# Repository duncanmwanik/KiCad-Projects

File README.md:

# A collection of my some of my PCB projects using KiCAD, with C++ and Flutter software.

# Smart Tap

# Laundry Machine Controller

# Fire Alarm Controller

# Ring Turn Page

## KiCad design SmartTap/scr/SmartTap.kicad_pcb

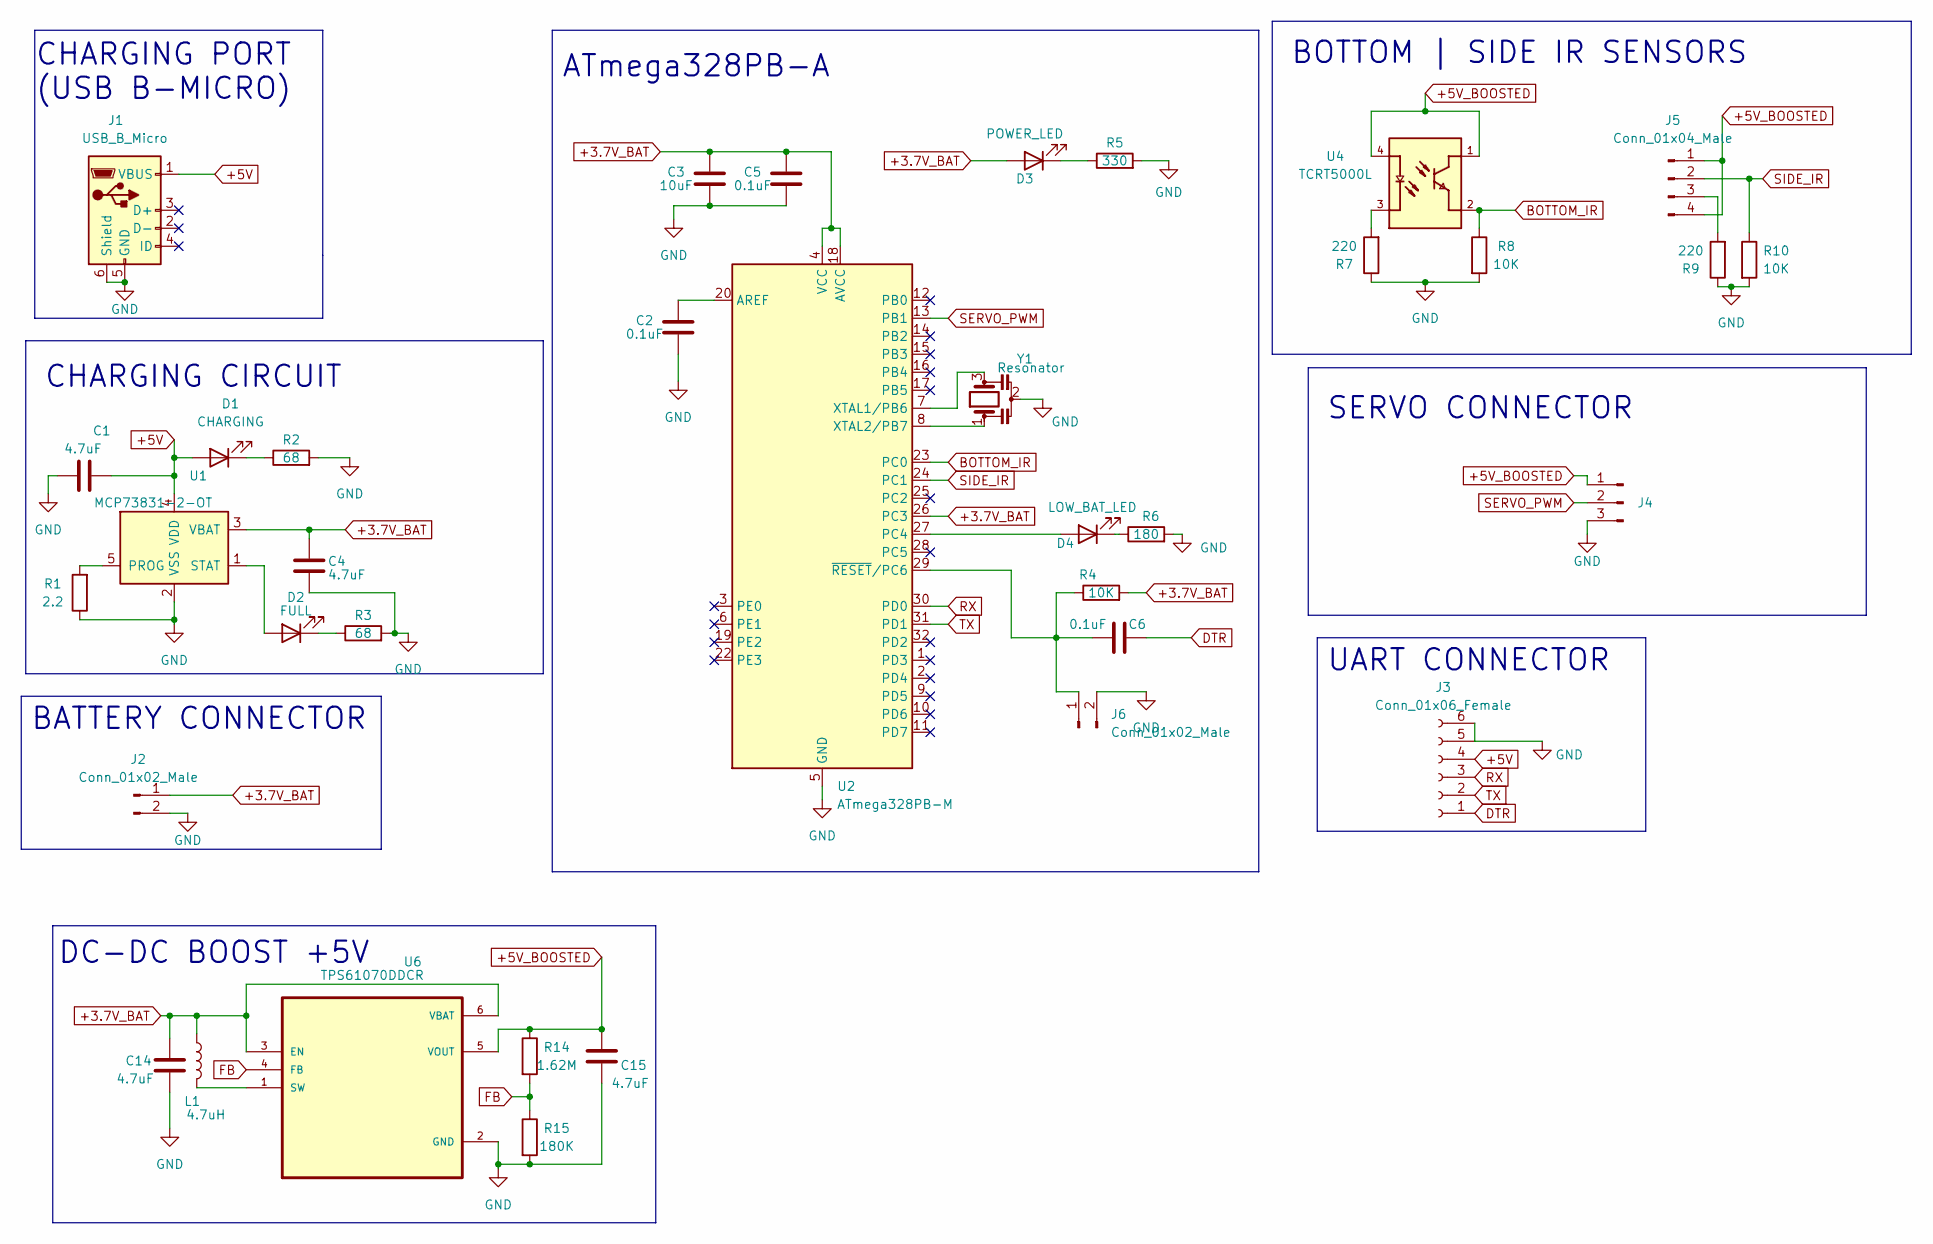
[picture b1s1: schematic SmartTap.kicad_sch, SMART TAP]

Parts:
C1, C4, C14, C15: 4.7uF; C_0402_1005Metric; MPN CL05A475KP5NRNC
C2, C5, C6: 0.1uF; C_0603_1608Metric; MPN CC0603JRNPO9BN200
C3: 10uF; C_0402_1005Metric; MPN CL05A106MQ5NUNC
D1: CHARGING; LED_0603_1608Metric; MPN 19-213/BHC-AP2Q2E/3T
D2: FULL; LED_0603_1608Metric; MPN 19-213/Y2C-CQ2R2L/3T(CY)
D3: POWER_LED; LED_0603_1608Metric; MPN 19-217/R6C-AL1M2VY/3T
D4: LOW_BAT_LED; LED_0603_1608Metric; MPN 19-213SURC/S530-A3/TR8
J1: USB_B_Micro; USB_Micro-B_Molex_47346-0001; MPN 473460001
J2: Conn_01x02_Male; WireConn1x02_P2.54mm
J3: Conn_01x06_Female; PinHeader_1x06_P2.54mm_Vertical; MPN B-2200S06P-A120
J4: Conn_01x03_Male; WireConn1x03_P2.54mm
J5: Conn_01x04_Male; WireConn1x04_P2.54mm
J6: Conn_01x02_Male; PinHeader_1x02_P2.54mm_Vertical
L1: 4.7uH; L_0603_1608Metric; MPN LQM18FN4R7M00D
R1: 2.2; R_0603_1608Metric; MPN 0603WAJ022JT5E
R2, R3: 68; R_0603_1608Metric; MPN 0603WAJ0680T5E
R4, R8, R10: 10K; R_0603_1608Metric; MPN 0603WAJ0103T5E
R5: 330; R_0603_1608Metric; MPN 0603WAJ0331T5E
R6: 180; R_0603_1608Metric; MPN 0603WAJ0181T5E
R7, R9: 220; R_0603_1608Metric; MPN 0603WAJ0221T5E
R14: 1.62M; R_0603_1608Metric; MPN 0603WAF1624T5E
R15: 180K; R_0603_1608Metric; MPN 0603WAF1803T5E
U1: MCP73831-2-OT; SOT-23-5; MPN MCP73831T-2ATI/OT
U2: ATmega328PB-M; QFN-32-1EP_5x5mm_P0.5mm_EP3.1x3.1mm; MPN ATMEGA328PB-MU
U4: TCRT5000L; XDCR_TCRT5000L
U6: TPS61070DDCR; SOT-23-6; MPN TPS61070DDCR
Y1: Resonator; OSC_CSTCE16M0V53-R0; MPN S2216000091080

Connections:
+3.7V_BAT: C3.2, C4.1, C5.2, C14.1, D3.2 (A), J2.1, L1.1, R4.2, U1.3 (VBAT), U2.4 (VCC), U2.18 (AVCC), U2.26 (PC3), U6.3 (EN), U6.6 (VBAT)
+5V: C1.2, D1.2 (A), J1.1 (VBUS), J3.4, U1.4 (VDD)
+5V_BOOSTED: C15.1, J4.1, J5.1, J5.4, R14.1, U4.1, U4.4, U6.5 (VOUT)
BOTTOM_IR: R8.1, U2.23 (PC0), U4.2
DTR: C6.2, J3.1
FB: R14.2, R15.1, U6.4 (FB)
GND: C1.1, C2.1, C3.1, C4.2, C5.1, C14.2, C15.2, J1.5 (GND), J1.6 (Shield), J2.2, J3.5, J3.6, J4.3, J6.2, R1.1, R2.2, R3.2, R5.2, R6.2, R7.1, R8.2, R9.1, R10.2, R15.2, U1.2 (VSS), U2.5 (GND), U2.21 (GND), U2.33 (GND), U6.2 (GND), Y1.2
unnamed: C2.2, U2.20 (AREF)
unnamed: C6.1, J6.1, R4.1, U2.29 (~RESET/PC6)
unnamed: D2.1 (K), R3.1
unnamed: D2.2 (A), U1.1 (STAT)
unnamed: D3.1 (K), R5.1
unnamed: D4.1 (K), R6.1
unnamed: D4.2 (A), U2.27 (PC4)
unnamed: J5.3, R9.2
unnamed: L1.2, U6.1 (SW)
unnamed: R1.2, U1.5 (PROG)
unnamed: D1.1 (K), R2.1
unnamed: R7.2, U4.3
unnamed: U2.7 (XTAL1/PB6), Y1.3
unnamed: U2.8 (XTAL2/PB7), Y1.1
RX: J3.3, U2.30 (PD0)
SERVO_PWM: J4.2, U2.13 (PB1)
SIDE_IR: J5.2, R10.1, U2.24 (PC1)
TX: J3.2, U2.31 (PD1)

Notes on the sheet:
SERVO CONNECTOR
CHARGING PORT (USB B-MICRO)
BOTTOM | SIDE IR SENSORS
DC-DC BOOST +5V
CHARGING CIRCUIT
BATTERY CONNECTOR
ATmega328PB-A
UART CONNECTOR

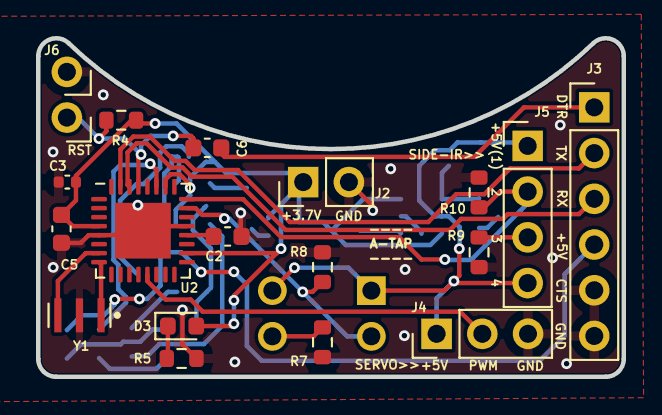
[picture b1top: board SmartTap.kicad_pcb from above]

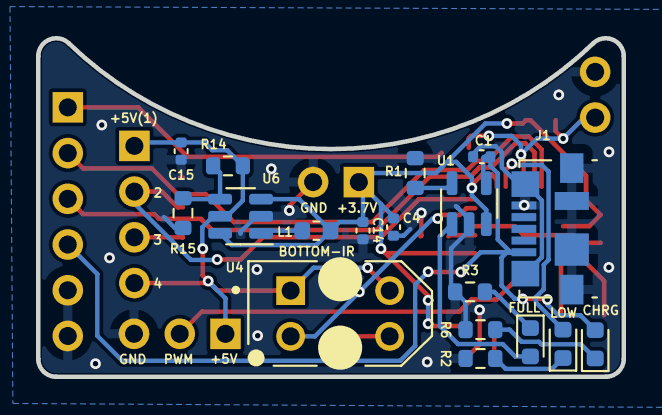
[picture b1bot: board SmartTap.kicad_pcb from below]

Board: 2 copper layers, 32.5 x 18.8 mm, 36 parts (18 on the bottom side), 25 nets.

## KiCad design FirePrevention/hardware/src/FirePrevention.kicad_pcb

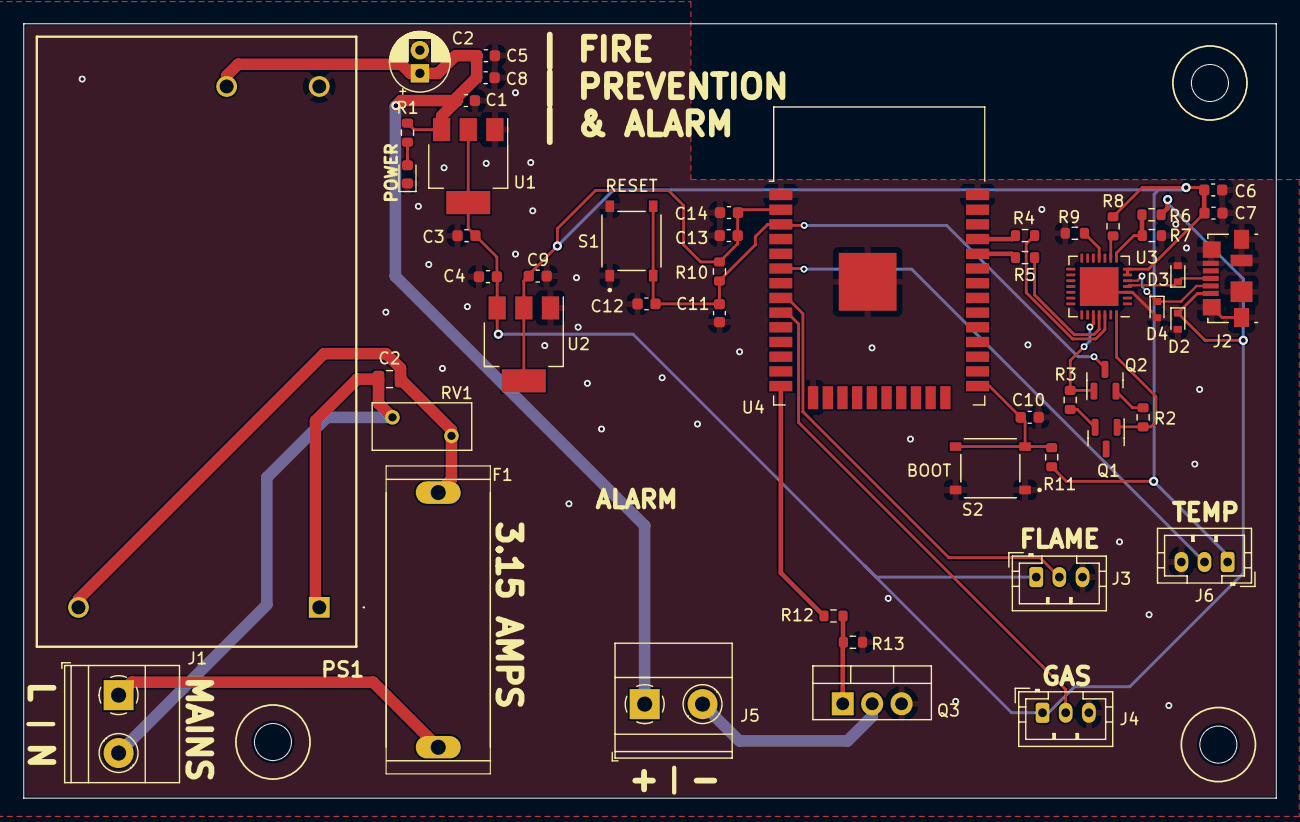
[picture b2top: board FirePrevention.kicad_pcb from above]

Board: 2 copper layers, 108.2 x 66.9 mm, 50 parts (0 on the bottom side), 29 nets.

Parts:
C1, C3, C5: 10uF/10V/10%; C_0603_1608Metric
C2: 22uF/50V/20%; CP_Radial_D5.0mm_P2.00mm
C2#2: 100nF; C_0805_2012Metric
C4, C8, C9, C14: 22uF/10V/10%; C_0603_1608Metric
C6: 4.7uF/50v; C_0603_1608Metric
C7, C10, C12: 0.1uF/50v; C_0603_1608Metric
C11: 0.1uF; C_0603_1608Metric
C13: 100nF/10V/10%; C_0603_1608Metric
D1: 12V; LED_0603_1608Metric
D2, D3, D4: D_TVS_Filled; D_SOD-523
F1: MC000827
J1: MAINS; TerminalBlock_Phoenix_MKDS-1,5-2_1x02_P5.00mm_Horizontal
J2: USB_B_Micro; USB_Micro-B_Molex_47346-0001
J3: FLAME_SENSOR_KYO26; JST_PH_B3B-PH-K_1x03_P2.00mm_Vertical
J4: GAS_SENSOR_MQ2; JST_PH_B3B-PH-K_1x03_P2.00mm_Vertical
J5: ALARM_SIREN_12V; TerminalBlock_Phoenix_MKDS-1,5-2_1x02_P5.00mm_Horizontal
J6: TEMPERATURE_SENSOR_DHT22; JST_PH_B3B-PH-K_1x03_P2.00mm_Vertical
PS1: RAC20E-12SK_277; RAC20E12SK277
Q1, Q2: SS8050; SOT-23
Q3: IRLZ44N; TO-220-3_Vertical
R1: 2k; R_0603_1608Metric
R2, R3, R10, R11: 10k; R_0603_1608Metric
R4, R5: 0R; R_0603_1608Metric
R6: 22.1K; R_0603_1608Metric
R7: 47.5K; R_0603_1608Metric
R8: 2K; R_0603_1608Metric
R9: 10K; R_0603_1608Metric
R12: 220/10V/5%; R_0603_1608Metric
R13: 47K/10V/5%; R_0603_1608Metric
RV1: Varistor; Fuse_BelFuse_0ZRE0005FF_L8.3mm_W3.8mm
S1, S2: TS-1187A-B-A-B; SW_TS-1187A-B-A-B
U1: AMS1117-5.0; SOT-223-3_TabPin2
U2: AMS1117-3.3; SOT-223-3_TabPin2
U3: CP2102N-Axx-xQFN28; QFN-28-1EP_5x5mm_P0.5mm_EP3.35x3.35mm
U4: ESP32-S; ESP32-WROOM-32

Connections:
+3V3: C6.2, C7.2, C9.1, C13.1, C14.1, J6.1, R8.2, R10.1, R11.1, U2.2 (VO), U3.6 (VDD), U3.7 (VREGIN), U4.2 (VDD)
+5V: C3.1, C4.1, D2.1 (A1), J2.1 (VBUS), J3.1, J4.1, R6.1, U1.2 (VO), U2.3 (VI)
+12V: C1.1, C2.1, C5.1, C8.1, J5.1, PS1.3 (_+VOUT), R1.1, U1.3 (VI)
/ALARM: R12.1, U4.14 (IO12)
/DTR: Q1.1 (E), R2.1, U3.28 (~DTR)
/EN: C11.1, C12.2, Q2.3 (C), R10.2, S1.C, S1.D, U4.3 (EN)
/FLAME: J3.2, U4.8 (IO32)
/GAS: J4.2, U4.9 (IO33)
/IO0: C10.2, R11.2, S2.C, S2.D, U4.25 (IO0)
/RTS: Q2.1 (E), R3.1, U3.24 (~RTS)
/RXD: R5.2, U3.25 (RXD)
/RXD0: R5.1, U4.34 (RXD0/IO3)
/TEMP: J6.2, U4.6 (IO34)
/TXD: R4.2, U3.26 (TXD)
/TXD0: R4.1, U4.35 (TXD0/IO1)
/USB_DN: D4.1 (A1), J2.2 (D-), U3.5 (D-)
/USB_DP: D3.1 (A1), J2.3 (D+), U3.4 (D+)
GND: C1.2, C2.2, C3.2, C4.2, C5.2, C6.1, C7.1, C8.2, C9.2, C10.1, C11.2, C12.1, C13.2, C14.2, D1.1 (K), D2.2 (A2), D3.2 (A2), D4.2 (A2), J2.5 (GND), J2.6 (Shield), J3.3, J4.3, J6.3, PS1.4 (-VOUT), Q3.3 (S), R7.1, R9.2, R13.1, S1.A, S1.B, S2.A, S2.B, U1.1 (GND), U2.1 (GND), U3.3 (GND), U3.29 (GND), U4.1 (GND), U4.15 (GND), U4.38 (GND), U4.39 (GND)
unnamed: D1.2 (A), R1.2
unnamed: F1.P$2, PS1.2 (VAC_IN_(L)), RV1.1
unnamed: F1.P$1, J1.1
unnamed: J1.2, PS1.1 (VAC_IN_(N)), RV1.2
unnamed: J5.2, Q3.2 (D)
unnamed: Q1.2 (B), R3.2
unnamed: Q2.2 (B), R2.2
unnamed: Q3.1 (G), R12.2, R13.2
unnamed: R6.2, R7.2, U3.8 (VBUS)
unnamed: R8.1, U3.9 (~RST)
unnamed: R9.1, U3.11 (~SUSPEND)

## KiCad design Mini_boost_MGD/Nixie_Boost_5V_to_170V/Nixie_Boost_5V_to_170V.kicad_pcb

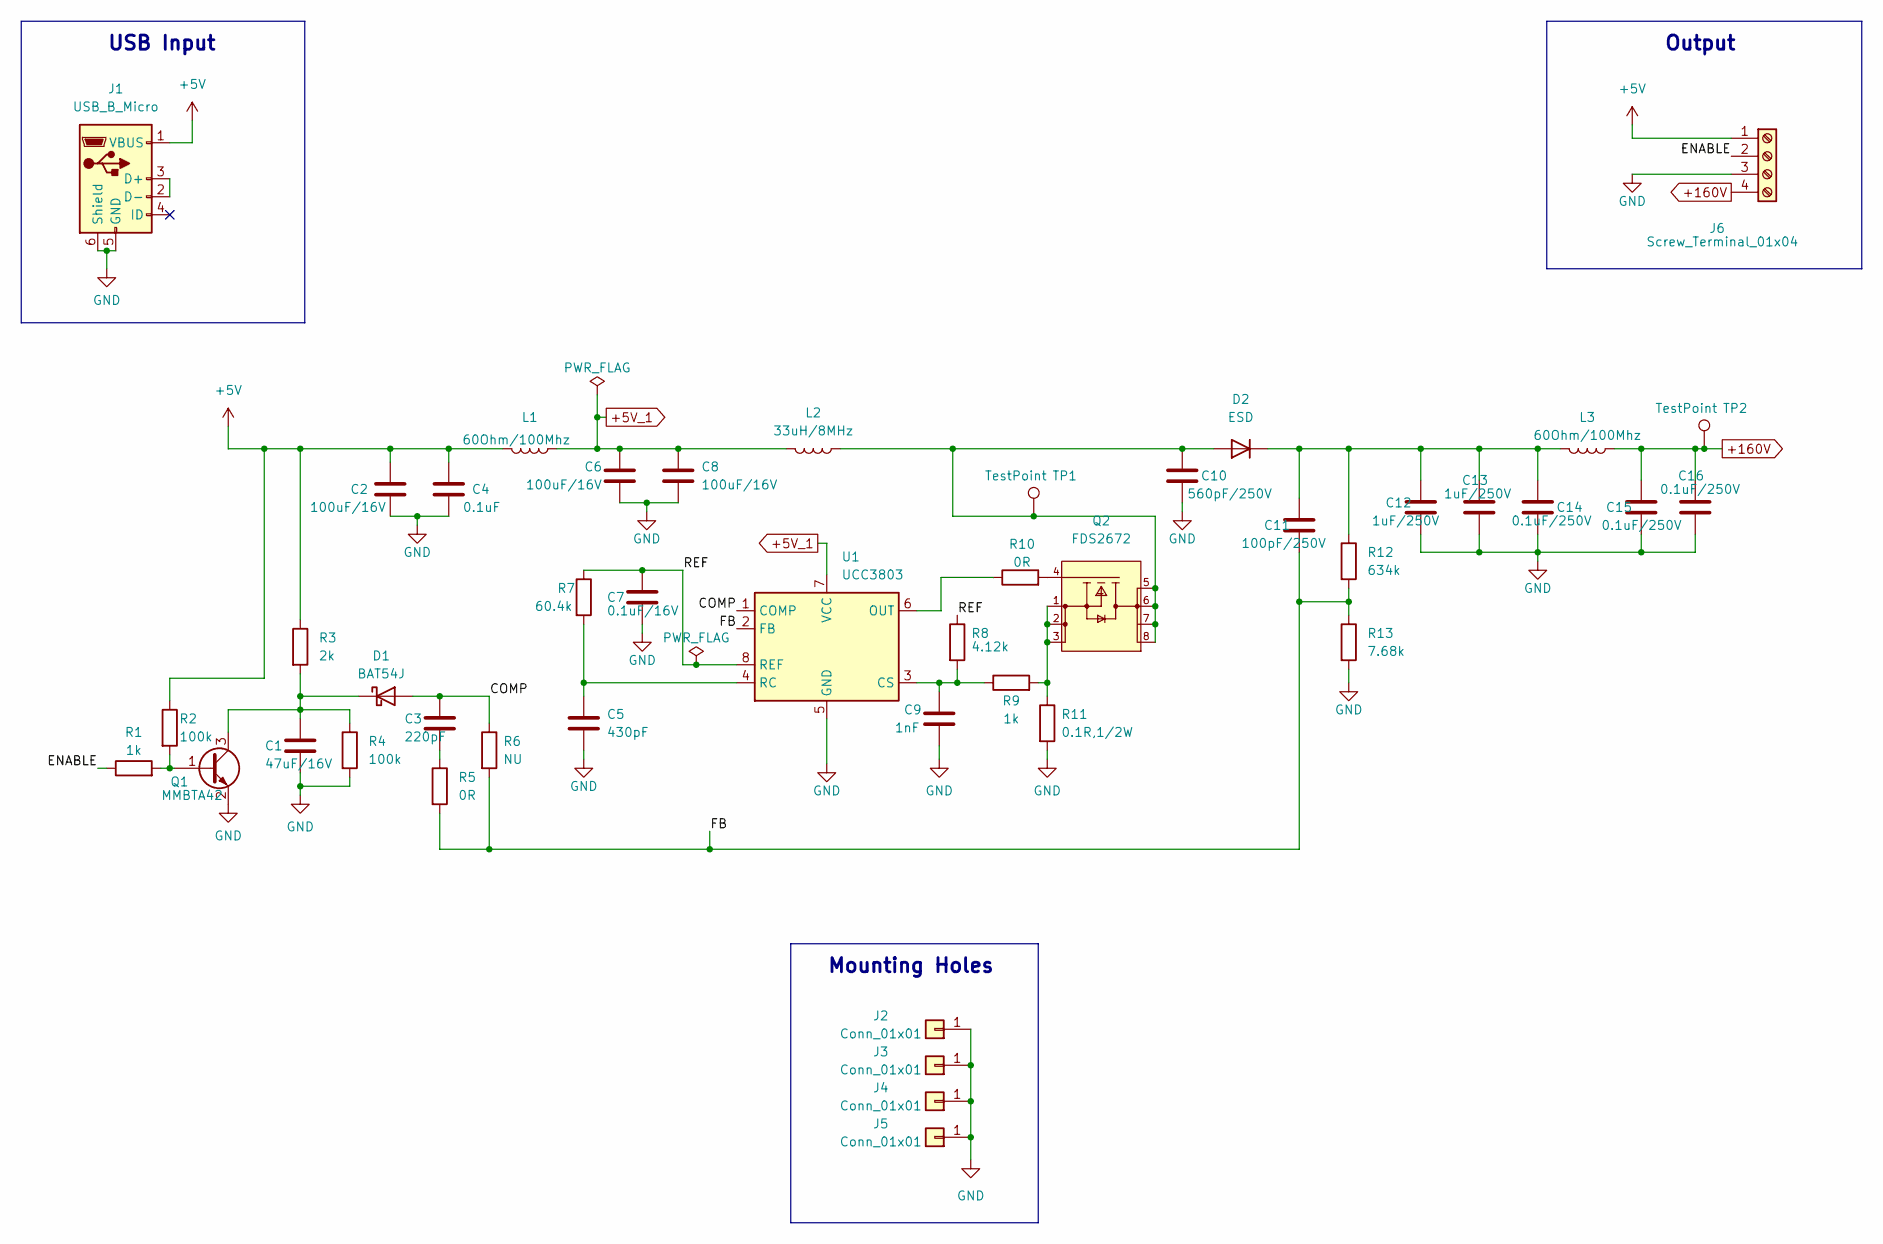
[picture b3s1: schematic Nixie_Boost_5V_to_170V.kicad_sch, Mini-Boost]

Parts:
C1: 47uF/16V; C_1206_3216Metric
C2, C6, C8: 100uF/16V; C_1210_3225Metric
C3: 220pF; C_0805_2012Metric
C4: 0.1uF; C_0805_2012Metric
C5: 430pF; C_0805_2012Metric
C7: 0.1uF/16V; C_0805_2012Metric
C9: 1nF; C_0805_2012Metric
C10: 560pF/250V; C_0603_1608Metric
C11: 100pF/250V; C_0805_2012Metric
C12, C13: 1uF/250V; C_0805_2012Metric
C14, C15, C16: 0.1uF/250V; C_0805_2012Metric
D1: BAT54J; D_SOD-323F
D2: ESD; D_SMA
J1: USB_B_Micro; USB_Micro-B_Molex_47346-0001
J2, J3, J4, J5: Conn_01x01; MountingHole_2.2mm_M2_Pad_Via
J6: Screw_Terminal_01x04; TerminalBlock_Phoenix_PT-1,5-4-3.5-H_1x04_P3.50mm_Horizontal
L1, L3: 60Ohm/100Mhz; L_0805_2012Metric; MPN BKP2125HS600-T
L2: 33uH/8MHz; L_12x12mm_H6mm; MPN 7447709330
Q1: MMBTA42; SOT-23
Q2: FDS2672; SOIC-8-1EP_3.9x4.9mm_P1.27mm_EP2.29x3mm
R1, R9: 1k; R_0805_2012Metric
R2, R4: 100k; R_0805_2012Metric
R3: 2k; R_0805_2012Metric
R5, R10: 0R; R_0805_2012Metric
R6: NU; R_0805_2012Metric
R7: 60.4k; R_0805_2012Metric
R8: 4.12k; R_0805_2012Metric
R11: 0.1R,1/2W; R_0805_2012Metric
R12: 634k; R_0805_2012Metric
R13: 7.68k; R_0805_2012Metric
TP1, TP2: TestPoint; TestPoint_Pad_D1.0mm
U1: UCC3803; SOIC-8-1EP_3.9x4.9mm_P1.27mm_EP2.29x3mm

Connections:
+5V: C2.1, C4.1, J1.1 (VBUS), J6.1, L1.2, R2.1, R3.1
+5V_1: C6.1, C8.1, L1.1, L2.2, U1.7 (VCC)
+160V: C15.1, C16.1, J6.4, L3.1, TP2.1
/COMP: C3.1, D1.2 (A), R6.1, U1.1 (COMP)
/ENABLE: J6.2, R1.1
/FB: C11.2, R5.2, R6.2, R12.2, R13.1, U1.2 (FB)
/REF: C7.1, R7.1, R8.1, U1.8 (REF)
GND: C1.2, C2.2, C4.2, C5.2, C6.2, C7.2, C8.2, C9.2, C10.2, C12.2, C13.2, C14.2, C15.2, C16.2, J1.5 (GND), J1.6 (Shield), J2.1, J3.1, J4.1, J5.1, J6.3, Q1.2 (E), R4.2, R11.2, R13.2, U1.5 (GND)
unnamed: C1.1, D1.1 (K), Q1.3 (C), R3.2, R4.1
unnamed: C3.2, R5.1
unnamed: C5.1, R7.2, U1.4 (RC)
unnamed: C9.1, R8.2, R9.1, U1.3 (CS)
unnamed: C10.1, D2.2 (A), L2.1, Q2.5 (D), Q2.6 (D), Q2.7 (D), Q2.8 (D), TP1.1
unnamed: C11.1, C12.1, C13.1, C14.1, D2.1 (K), L3.2, R12.1
unnamed: J1.2 (D-), J1.3 (D+)
unnamed: Q1.1 (B), R1.2, R2.2
unnamed: Q2.1 (S), Q2.2 (S), Q2.3 (S), R9.2, R11.1
unnamed: Q2.4 (S), R10.2
unnamed: R10.1, U1.6 (OUT)

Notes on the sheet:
USB Input
Mounting Holes
Output

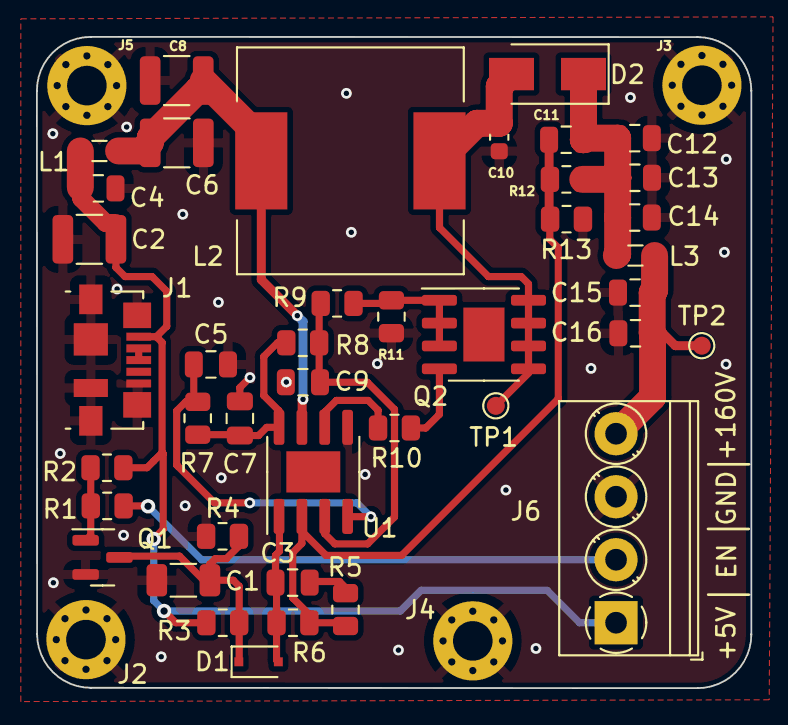
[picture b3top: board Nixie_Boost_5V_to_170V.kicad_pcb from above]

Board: 2 copper layers, 39.7 x 36.2 mm, 45 parts (0 on the bottom side), 19 nets.

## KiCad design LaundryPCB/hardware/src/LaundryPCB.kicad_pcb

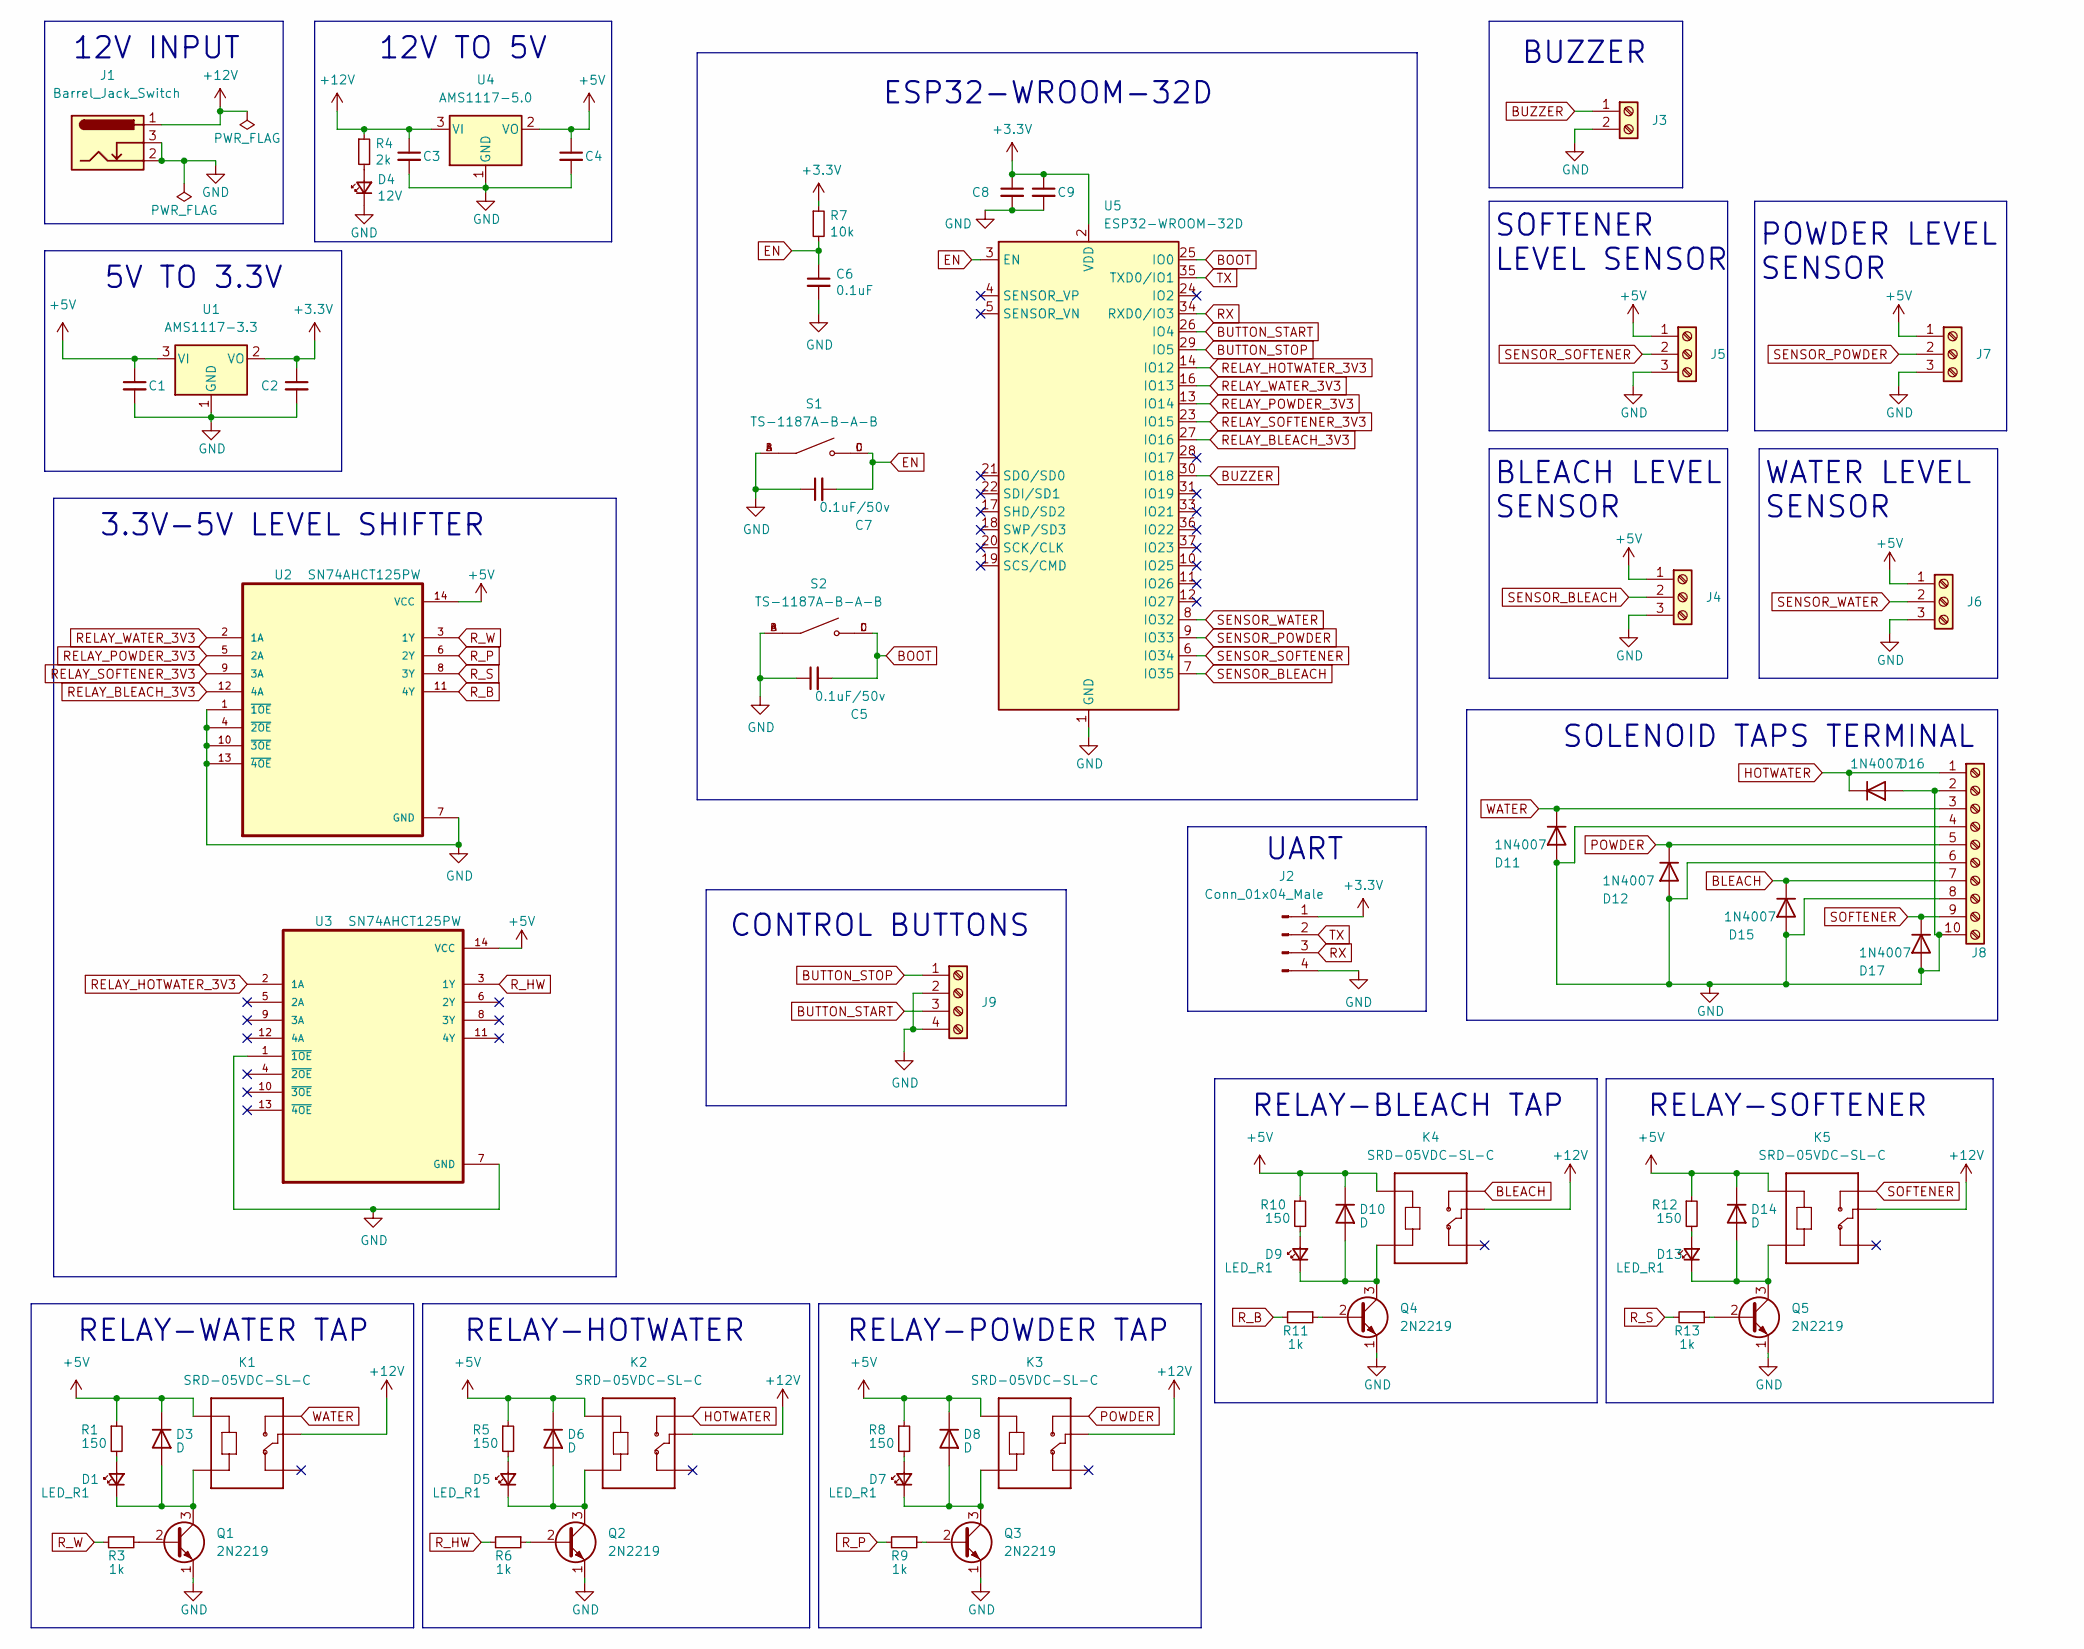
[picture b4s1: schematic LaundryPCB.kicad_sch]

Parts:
C1, C2, C9: 22uF/10V/10%; C_0603_1608Metric
C3, C4: 10uF/10V/10%; C_0603_1608Metric
C5, C7: 0.1uF/50v; C_0603_1608Metric
C6: 0.1uF; C_0603_1608Metric
C8: 100nF/10V/10%; C_0603_1608Metric
D1, D5, D7, D9, D13: LED_R1; LED_0603_1608Metric
D3, D6, D8, D10, D14: D; D_0603_1608Metric
D4: 12V; LED_0603_1608Metric
D11, D12, D15, D16, D17: 1N4007; D_DO-41_SOD81_P10.16mm_Horizontal
J1: Barrel_Jack_Switch; BarrelJack_Horizontal
J2: Conn_01x04_Male; PinHeader_1x04_P2.54mm_Vertical
J3: Screw_Terminal_01x02; TerminalBlock_Phoenix_MKDS-3-2-5.08_1x02_P5.08mm_Horizontal
J4, J5, J6, J7: Screw_Terminal_01x03; TerminalBlock_Phoenix_MKDS-3-3-5.08_1x03_P5.08mm_Horizontal
J8: Screw_Terminal_01x10; TerminalBlock_Phoenix_MKDS-1,5-10-5.08_1x10_P5.08mm_Horizon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
J9: Screw_Terminal_01x04; TerminalBlock_Phoenix_MKDS-1,5-4-5.08_1x04_P5.08mm_Horizont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
K1, K2, K3, K4, K5: SRD-05VDC-SL-C; RELAY_SRD-05VDC-SL-C
Q1, Q2, Q3, Q4, Q5: 2N2219; SOT-23
R1, R5, R8, R10, R12: 150; R_0603_1608Metric
R3, R6, R9, R11, R13: 1k; R_0603_1608Metric
R4: 2k; R_0603_1608Metric
R7: 10k; R_0603_1608Metric
S1, S2: TS-1187A-B-A-B; SW_TS-1187A-B-A-B; PARTREV A0
U1: AMS1117-3.3; SOT-223-3_TabPin2
U2, U3: SN74AHCT125PW; SOP65P640X120-14N
U4: AMS1117-5.0; SOT-223-3_TabPin2
U5: ESP32-WROOM-32D; ESP32-WROOM-32

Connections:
+3V3: C2.1, C8.1, C9.1, J2.1, R7.1, U1.2 (VO), U5.2 (VDD)
+5V: C1.1, C4.1, D3.1 (K), D6.1 (K), D8.1 (K), D10.1 (K), D14.1 (K), J4.1, J5.1, J6.1, J7.1, K1.A1, K2.A1, K3.A1, K4.A1, K5.A1, R1.1, R5.1, R8.1, R10.1, R12.1, U1.3 (VI), U2.14 (VCC), U3.14 (VCC), U4.2 (VO)
+12V: C3.1, J1.1, K1.COM, K2.COM, K3.COM, K4.COM, K5.COM, R4.1, U4.3 (VI)
BLEACH: D15.1 (K), J8.7, K4.NO
BOOT: C5.2, S2.C, S2.D, U5.25 (IO0)
BUTTON_START: J9.3, U5.26 (IO4)
BUTTON_STOP: J9.1, U5.29 (IO5)
BUZZER: J3.1, U5.30 (IO18)
EN: C6.1, C7.2, R7.2, S1.C, S1.D, U5.3 (EN)
GND: C1.2, C2.2, C3.2, C4.2, C5.1, C6.2, C7.1, C8.2, C9.2, D4.1 (K), D11.2 (A), D12.2 (A), D15.2 (A), D16.2 (A), D17.2 (A), J1.2, J1.3, J2.4, J3.2, J4.3, J5.3, J6.3, J7.3, J8.2, J8.4, J8.6, J8.8, J8.10, J9.2, J9.4, Q1.1 (E), Q2.1 (E), Q3.1 (E), Q4.1 (E), Q5.1 (E), S1.A, S1.B, S2.A, S2.B, U1.1 (GND), U2.1 (~1OE), U2.4 (~2OE), U2.7 (GND), U2.10 (~3OE), U2.13 (~4OE), U3.1 (~1OE), U3.7 (GND), U4.1 (GND), U5.1 (GND), U5.15 (GND), U5.38 (GND), U5.39 (GND)
HOTWATER: D16.1 (K), J8.1, K2.NO
unnamed: D1.1 (K), D3.2 (A), K1.A2, Q1.3 (C)
unnamed: D1.2 (A), R1.2
unnamed: D4.2 (A), R4.2
unnamed: D5.1 (K), D6.2 (A), K2.A2, Q2.3 (C)
unnamed: D5.2 (A), R5.2
unnamed: D7.1 (K), D8.2 (A), K3.A2, Q3.3 (C)
unnamed: D7.2 (A), R8.2
unnamed: D9.2 (A), R10.2
unnamed: D9.1 (K), D10.2 (A), K4.A2, Q4.3 (C)
unnamed: D13.1 (K), D14.2 (A), K5.A2, Q5.3 (C)
unnamed: D13.2 (A), R12.2
unnamed: Q1.2 (B), R3.1
unnamed: Q2.2 (B), R6.1
unnamed: Q3.2 (B), R9.1
unnamed: Q4.2 (B), R11.1
unnamed: Q5.2 (B), R13.1
POWDER: D12.1 (K), J8.5, K3.NO
RELAY_BLEACH_3V3: U2.12 (4A), U5.27 (IO16)
RELAY_HOTWATER_3V3: U3.2 (1A), U5.14 (IO12)
RELAY_POWDER_3V3: U2.5 (2A), U5.13 (IO14)
RELAY_SOFTENER_3V3: U2.9 (3A), U5.23 (IO15)
RELAY_WATER_3V3: U2.2 (1A), U5.16 (IO13)
RX: J2.3, U5.34 (RXD0/IO3)
R_B: R11.2, U2.11 (4Y)
R_HW: R6.2, U3.3 (1Y)
R_P: R9.2, U2.6 (2Y)
R_S: R13.2, U2.8 (3Y)
R_W: R3.2, U2.3 (1Y)
SENSOR_BLEACH: J4.2, U5.7 (IO35)
SENSOR_POWDER: J7.2, U5.9 (IO33)
SENSOR_SOFTENER: J5.2, U5.6 (IO34)
SENSOR_WATER: J6.2, U5.8 (IO32)
SOFTENER: D17.1 (K), J8.9, K5.NO
TX: J2.2, U5.35 (TXD0/IO1)
WATER: D11.1 (K), J8.3, K1.NO

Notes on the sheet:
RELAY-HOTWATER
RELAY-SOFTENER
SOFTENER LEVEL SENSOR
RELAY-BLEACH TAP
ESP32-WROOM-32D
RELAY-POWDER TAP
UART
RELAY-WATER TAP
3.3V-5V LEVEL SHIFTER
WATER LEVEL SENSOR
12V TO 5V
SOLENOID TAPS TERMINAL
BLEACH LEVEL SENSOR
5V TO 3.3V
12V INPUT
POWDER LEVEL SENSOR
CONTROL BUTTONS
BUZZER

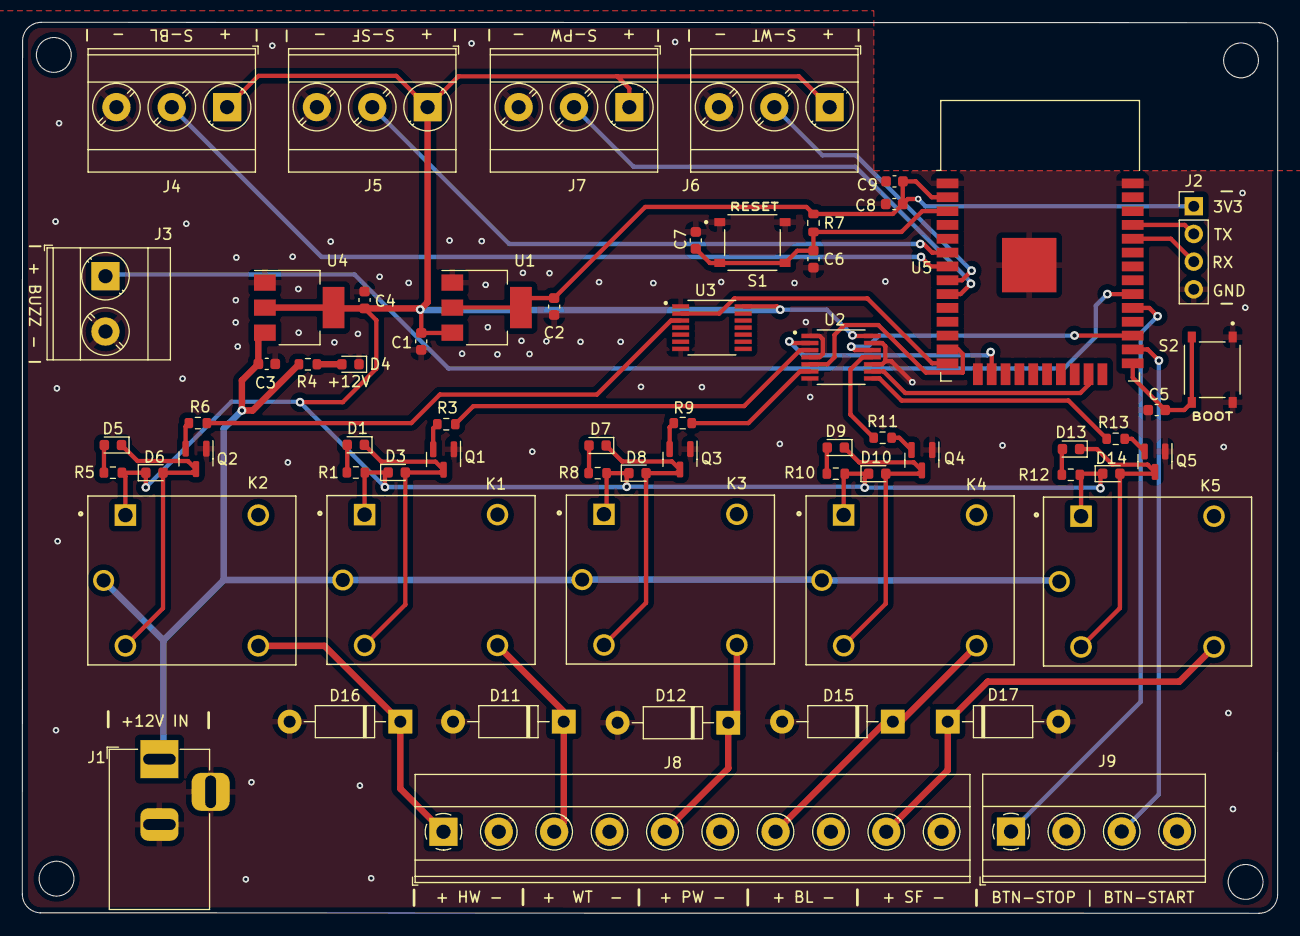
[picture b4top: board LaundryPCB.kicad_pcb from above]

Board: 2 copper layers, 115.2 x 81.8 mm, 63 parts (0 on the bottom side), 46 nets.

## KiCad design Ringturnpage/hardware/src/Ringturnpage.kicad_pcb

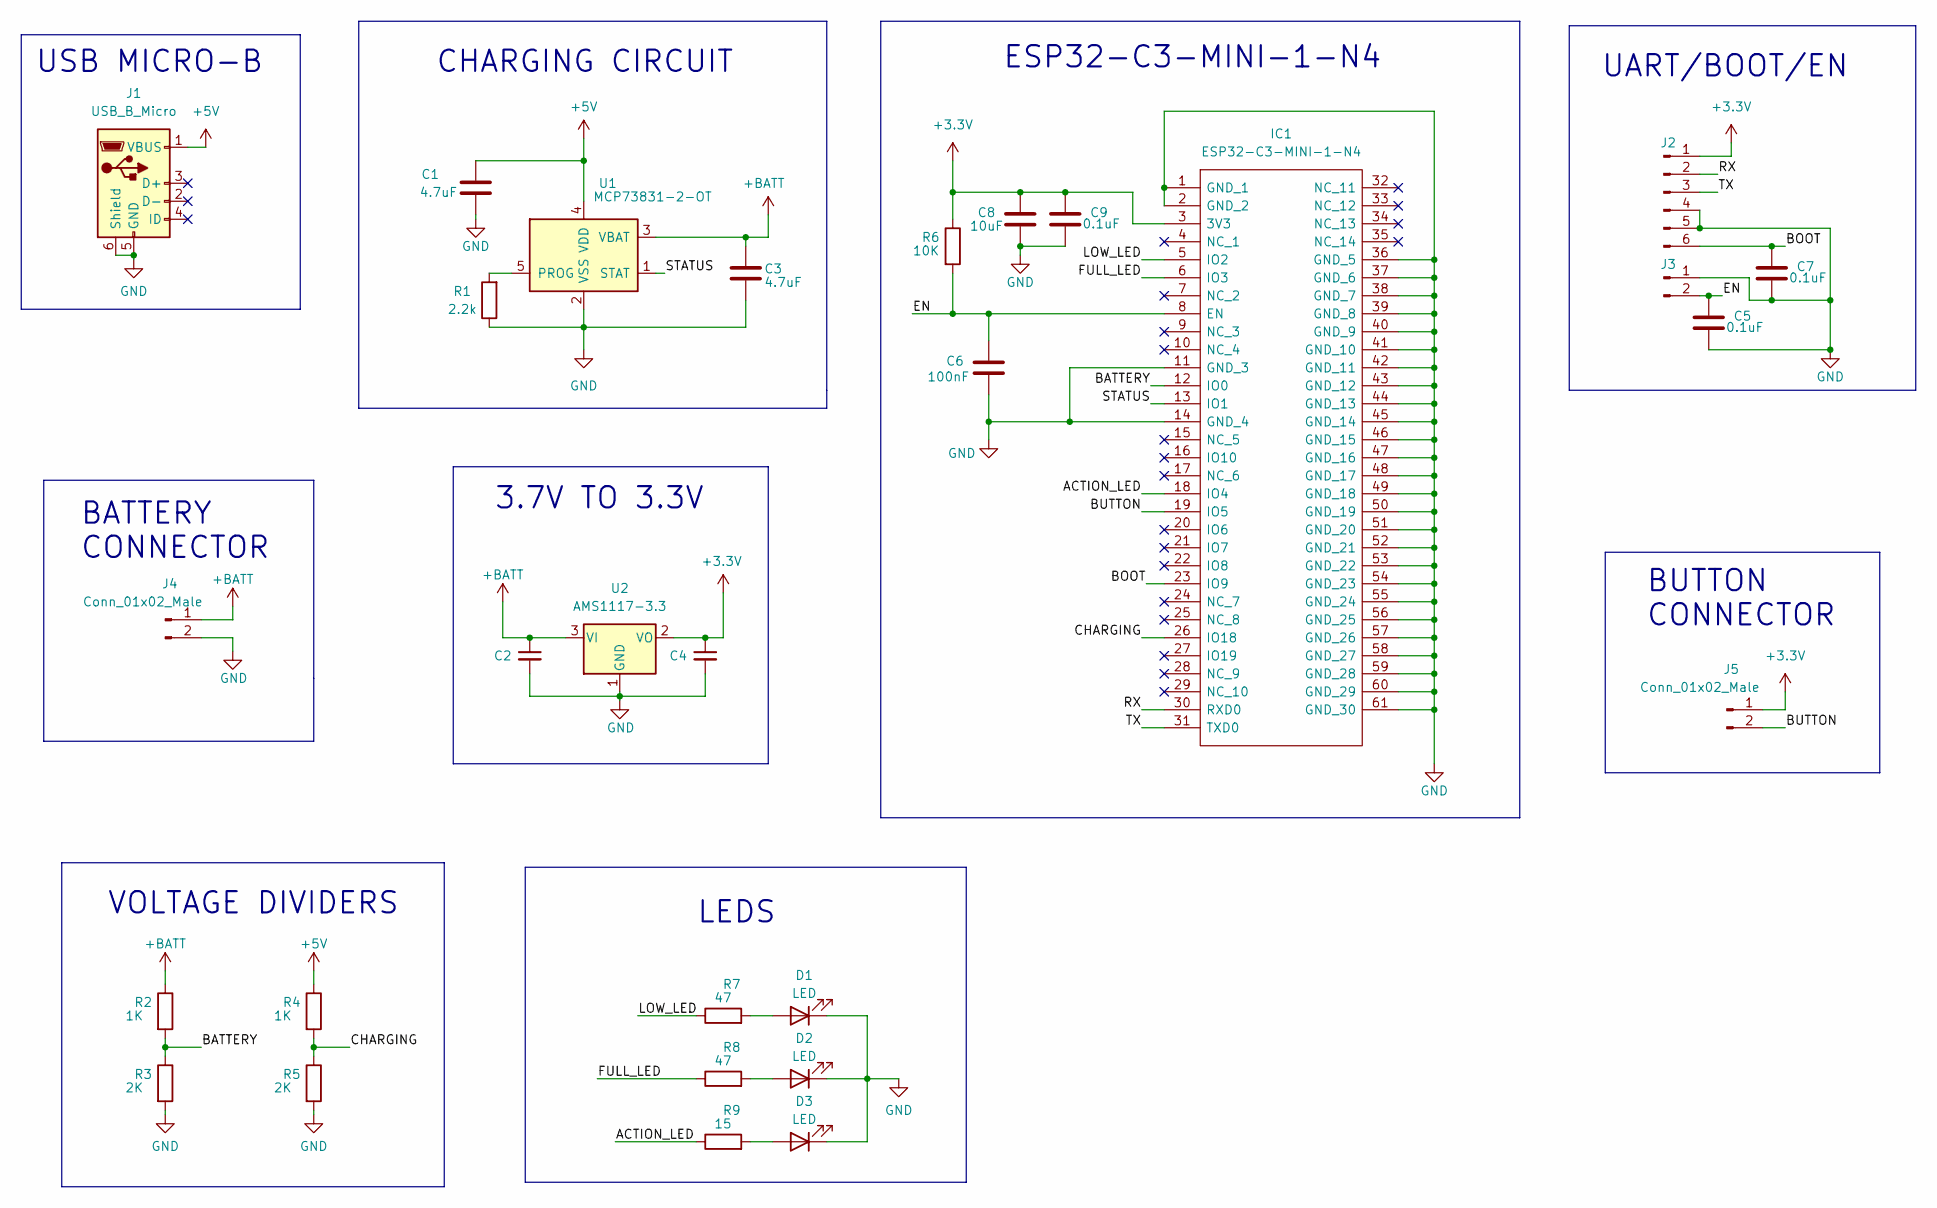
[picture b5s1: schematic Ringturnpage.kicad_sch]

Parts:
C1, C3: 4.7uF; C_0402_1005Metric; MPN CL05A475KP5NRNC
C2, C4: 22uF/10V/10%; C_0402_1005Metric; MPN CL05A226MQ6ZUN8
C5, C7, C9: 0.1uF; C_0402_1005Metric; MPN CL05B104KO5NNNC
C6: 100nF; C_0402_1005Metric; MPN CL05B104KO5NNNC
C8: 10uF; C_0402_1005Metric; MPN CC0402KRX7R7BB104
D1: LED; LED_0402_1005Metric; MPN 16-213/SDRC/S530-A3/TR8
D2: LED; LED_0402_1005Metric; MPN 16-213SYGC/S530-E3/TR8
D3: LED; LED_0402_1005Metric; MPN 16-213/BHC-ZL1M2B6Y/3T
IC1: ESP32-C3-MINI-1-N4; ESP32C3MINI1N4; Manufacturer_Part_Number ESP32-C3-MINI-1-N4; Mouser Part Number 356-ESP32-C3-MINI1N4
J1: USB_B_Micro; USB_Micro-B_Molex_47346-0001; MPN 47346-0001
J2: Conn_01x06_Male; PinHeader_1x06_P2.54mm_Vertical; MPN B-2100S06P-A110
J3: Conn_01x02_Male; PinHeader_1x02_P2.54mm_Vertical; MPN B-2100S02P-A110
J4: Conn_01x02_Male; JST_PH_B2B-PH-K_1x02_P2.00mm_Vertical; MPN JST_PH_B2B-PH-K_1x02_P2.00mm_Vertical
J5: Conn_01x02_Male; TestPoint_2Pads_Pitch2.54mm_Drill0.8mm
R1: 2.2k; R_0402_1005Metric; MPN 0603WAJ022JT5E
R2, R4: 1K; R_0402_1005Metric; MPN RC0402JR-071KL
R3, R5: 2K; R_0402_1005Metric; MPN RC0402JR-072KL
R6: 10K; R_0402_1005Metric; MPN RC0402FR-0710KL
R7, R8: 47; R_0402_1005Metric; MPN RC0402FR-0747RL
R9: 15; R_0402_1005Metric; MPN RC0402FR-0715RL
U1: MCP73831-2-OT; SOT-23-5; MPN MCP73831T-2ATI/OT
U2: AMS1117-3.3; SOT-223-3_TabPin2; MPN AMS1117-3.3

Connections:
+3V3: C4.1, C8.2, C9.1, IC1.3 (3V3), J2.1, J5.1, R6.1, U2.2 (VO)
+5V: C1.2, J1.1 (VBUS), R4.1, U1.4 (VDD)
+BATT: C2.1, C3.1, J4.1, R2.1, U1.3 (VBAT), U2.3 (VI)
/ACTION_LED: IC1.18 (IO4), R9.1
/BATTERY: IC1.12 (IO0), R2.2, R3.1
/BOOT: C7.1, IC1.23 (IO9), J2.6
/BUTTON: IC1.19 (IO5), J5.2
/CHARGING: IC1.26 (IO18), R4.2, R5.1
/EN: C5.1, C6.2, IC1.8 (EN), J3.2, R6.2
/FULL_LED: IC1.6 (IO3), R8.1
/LOW_LED: IC1.5 (IO2), R7.1
/RX: IC1.30 (RXD0), J2.2
/STATUS: IC1.13 (IO1), U1.1 (STAT)
/TX: IC1.31 (TXD0), J2.3
GND: C1.1, C2.2, C3.2, C4.2, C5.2, C6.1, C7.2, C8.1, C9.2, D1.1 (K), D2.1 (K), D3.1 (K), IC1.1 (GND_1), IC1.2 (GND_2), IC1.11 (GND_3), IC1.14 (GND_4), IC1.36 (GND_5), IC1.37 (GND_6), IC1.38 (GND_7), IC1.39 (GND_8), IC1.40 (GND_9), IC1.41 (GND_10), IC1.42 (GND_11), IC1.43 (GND_12), IC1.44 (GND_13), IC1.45 (GND_14), IC1.46 (GND_15), IC1.47 (GND_16), IC1.48 (GND_17), IC1.49 (GND_18), IC1.50 (GND_19), IC1.51 (GND_20), IC1.52 (GND_21), IC1.53 (GND_22), IC1.54 (GND_23), IC1.55 (GND_24), IC1.56 (GND_25), IC1.57 (GND_26), IC1.58 (GND_27), IC1.59 (GND_28), IC1.60 (GND_29), IC1.61 (GND_30), J1.5 (GND), J1.6 (Shield), J2.4, J2.5, J3.1, J4.2, R1.1, R3.2, R5.2, U1.2 (VSS), U2.1 (GND)
unnamed: D1.2 (A), R7.2
unnamed: D2.2 (A), R8.2
unnamed: D3.2 (A), R9.2
unnamed: R1.2, U1.5 (PROG)

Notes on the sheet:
LEDS
CHARGING CIRCUIT
VOLTAGE DIVIDERS
UART/BOOT/EN
ESP32-C3-MINI-1-N4
3.7V TO 3.3V
USB MICRO-B
BATTERY CONNECTOR
BUTTON CONNECTOR
